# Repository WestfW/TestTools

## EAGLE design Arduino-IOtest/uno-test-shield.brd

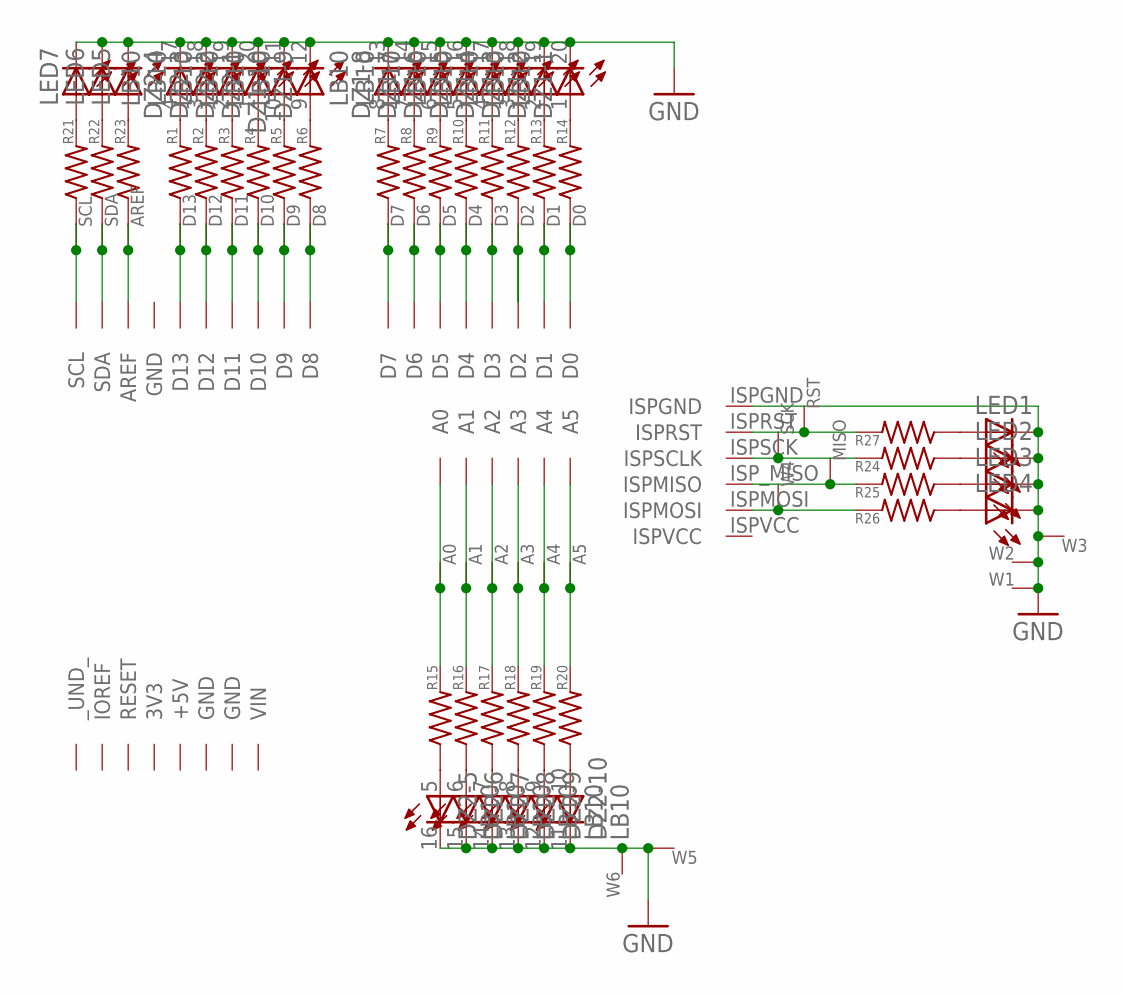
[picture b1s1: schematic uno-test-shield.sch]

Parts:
A0, A1, A2, A3, A4, A5: WIRE-VIA11; VIA11
AREF: WIRE-VIA11; VIA11
D0, D1, D2, D3, D4, D5, D6, D7, D8, D9, D10, D11, D12, D13: WIRE-VIA11; VIA11
DZ1, DZ2: LB10
LED1, LED2, LED3, LED4, LED5, LED6, LED7: LED3MM
MISO: WIRE-VIA11; VIA11
R1, R2, R3, R4, R5, R6, R7, R8, R9, R10, R11, R12, R13, R14, R15, R16, R17, R18, R19, R20, R21, R22, R23, R24, R25, R26, R27: R-US_R0805; R0805
RST: WIRE-VIA11; VIA11
SCK: WIRE-VIA11; VIA11
SCL: WIRE-VIA11; VIA11
SDA: WIRE-VIA11; VIA11
U$1: ARDUINO-R3ALLNOHOLES; R3+ISP-NOHOLES
W1, W2, W3, W4, W5, W6: WIRE-VIA11; VIA11

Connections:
3V3: U$1.PWR+3V (3V3)
+5V: U$1.PWR+5 (+5V)
AREF: AREF.P$1, R23.1, U$1.DAREF (AREF)
D0: D0.P$1, R14.1, U$1.D0
GND: DZ1.11 (C), DZ1.12 (C), DZ1.13 (C), DZ1.14 (C), DZ1.15 (C), DZ1.16 (C), DZ1.17 (C), DZ1.18 (C), DZ1.19 (C), DZ1.20 (C), DZ2.11 (C), DZ2.12 (C), DZ2.13 (C), DZ2.14 (C), DZ2.15 (C), DZ2.16 (C), DZ2.17 (C), DZ2.18 (C), DZ2.19 (C), DZ2.20 (C), LED1.K (C), LED2.K (C), LED3.K (C), LED4.K (C), LED5.K (C), LED6.K (C), LED7.K (C), U$1.DGND (GND), U$1.ISPGND, U$1.PWRGND1 (GND), U$1.PWRGND2 (GND), W1.P$1, W2.P$1, W3.P$1, W5.P$1, W6.P$1
ISPVCC: U$1.ISPVCC
MISO: MISO.P$1, R25.2, U$1.ISP_MISO (ISPMISO)
MOSI: R26.2, U$1.ISPMOSI, W4.P$1
unnamed: D13.P$1, R1.1, U$1.D13
unnamed: DZ2.4 (A), R1.2
unnamed: D12.P$1, R2.1, U$1.D12
unnamed: DZ2.3 (A), R2.2
unnamed: D11.P$1, R3.1, U$1.D11
unnamed: DZ2.2 (A), R3.2
unnamed: D10.P$1, R4.1, U$1.D10
unnamed: DZ2.1 (A), R4.2
unnamed: D9.P$1, R5.1, U$1.D9
unnamed: DZ1.10 (A), R5.2
unnamed: D8.P$1, R6.1, U$1.D8
unnamed: DZ1.9 (A), R6.2
unnamed: D7.P$1, R7.1, U$1.D7
unnamed: DZ1.8 (A), R7.2
unnamed: D6.P$1, R8.1, U$1.D6
unnamed: DZ1.7 (A), R8.2
unnamed: D5.P$1, R9.1, U$1.D5
unnamed: DZ1.6 (A), R9.2
unnamed: D4.P$1, R10.1, U$1.D4
unnamed: DZ1.5 (A), R10.2
unnamed: D3.P$1, R11.1, U$1.D3
unnamed: DZ1.4 (A), R11.2
unnamed: D2.P$1, R12.1, U$1.D2
unnamed: DZ1.3 (A), R12.2
unnamed: D1.P$1, R13.1, U$1.D1
unnamed: DZ1.2 (A), R13.2
unnamed: DZ1.1 (A), R14.2
unnamed: A0.P$1, R15.2, U$1.A0
unnamed: DZ2.5 (A), R15.1
unnamed: A1.P$1, R16.2, U$1.A1
unnamed: DZ2.6 (A), R16.1
unnamed: A2.P$1, R17.2, U$1.A2
unnamed: DZ2.7 (A), R17.1
unnamed: A3.P$1, R18.2, U$1.A3
unnamed: DZ2.8 (A), R18.1
unnamed: A4.P$1, R19.2, U$1.A4
unnamed: DZ2.9 (A), R19.1
unnamed: A5.P$1, R20.2, U$1.A5
unnamed: DZ2.10 (A), R20.1
unnamed: LED1.A, R27.1
unnamed: LED2.A, R24.1
unnamed: LED3.A, R25.1
unnamed: LED4.A, R26.1
unnamed: LED5.A, R23.2
unnamed: LED6.A, R22.2
unnamed: LED7.A, R21.2
RST: R27.2, RST.P$1, U$1.ISPRST
SCK: R24.2, SCK.P$1, U$1.ISPSCK (ISPSCLK)
SCL: R21.1, SCL.P$1, U$1.DSCL (SCL)
SDA: R22.1, SDA.P$1, U$1.DSDA (SDA)
VIN: U$1.PWRVIN (VIN)

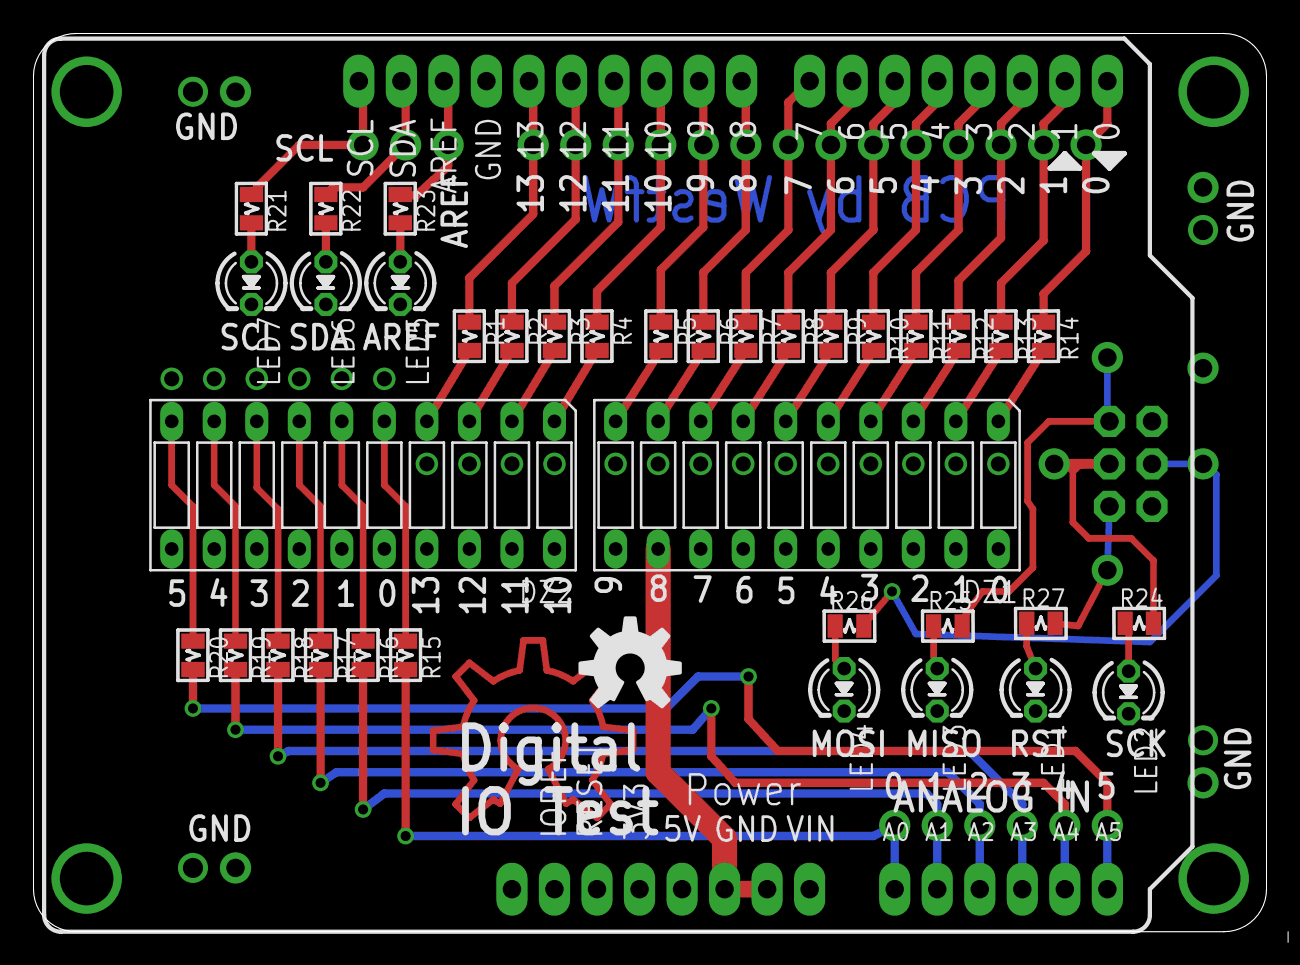
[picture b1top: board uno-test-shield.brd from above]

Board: 2 copper layers, 73.6 x 53.6 mm, 69 parts (0 on the bottom side), 55 nets.

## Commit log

2019-11-25 Add uno-test-shield
